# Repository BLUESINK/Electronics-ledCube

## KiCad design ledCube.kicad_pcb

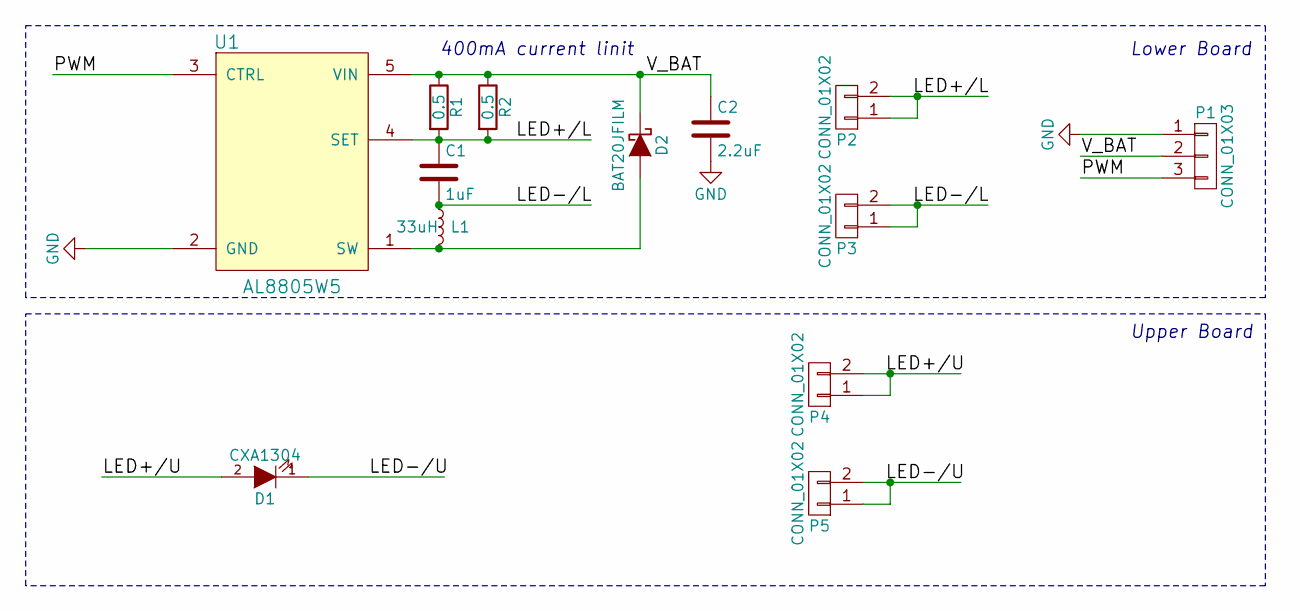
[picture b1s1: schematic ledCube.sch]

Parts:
C1: 1uF; C_0805
C2: 2.2uF; C_0805
D1: CXA1304; Part # CXA1304-0000-000N00B440F-ND
D2: BAT20JFILM; SOD-323_HandSoldering; Part # 497-3381-1-ND
L1: 33uH; inductor_33uH; Part # SRN6045-330MCT-ND
P1: CONN_01X03; Socket_Strip_Straight_1x03
P2, P3, P4, P5: CONN_01X02; Socket_Strip_Straight_1x02
R1, R2: 0.5; R_1206; Part # 311-0.5LWCT-ND
U1: AL8805W5; SOT-23-5; Part # AL8805W5-7DICT-ND

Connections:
/LED+/L: C1.1, P2.1, P2.2, R1.2, R2.2, U1.4 (SET)
/LED+/U: D1.2 (A), P4.1, P4.2
/LED-/L: C1.2, L1.1, P3.1, P3.2
/LED-/U: D1.1 (K), P5.1, P5.2
/PWM: P1.3, U1.3 (CTRL)
/V_BAT: C2.1, D2.1 (K), P1.2, R1.1, R2.1, U1.5 (VIN)
GND: C2.2, P1.1, U1.2 (GND)
unnamed: D2.2 (A), L1.2, U1.1 (SW)

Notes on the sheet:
400mA current linit
Lower Board
Upper Board

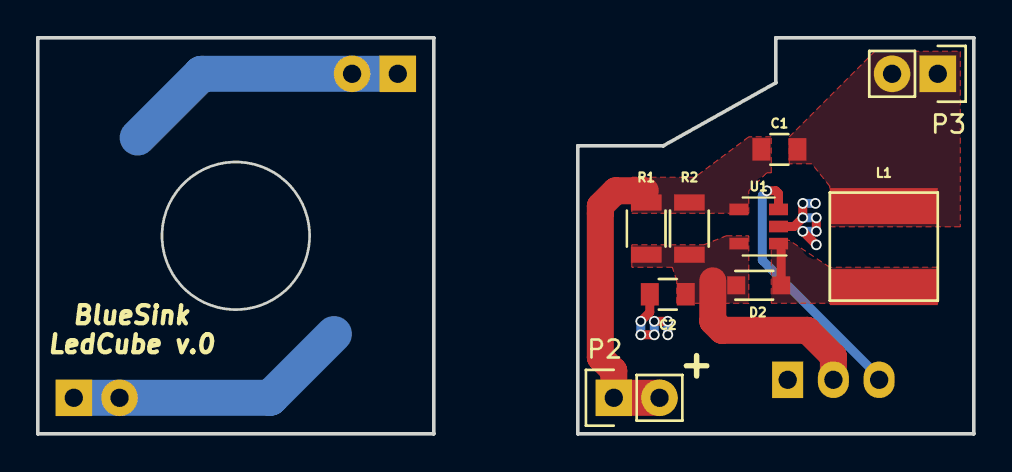
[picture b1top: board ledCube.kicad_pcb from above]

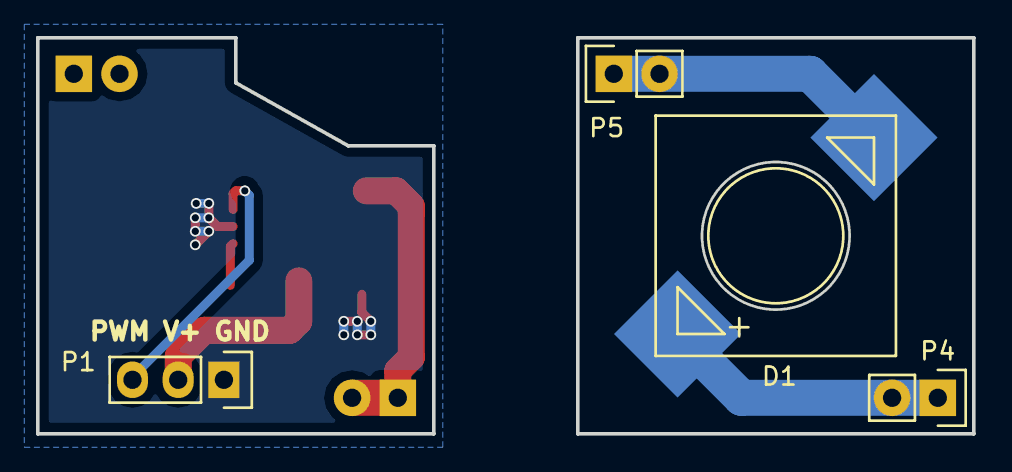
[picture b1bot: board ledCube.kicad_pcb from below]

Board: 2 copper layers, 52.0 x 22.0 mm, 13 parts (4 on the bottom side), 8 nets.

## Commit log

2016-12-28 Generate BOM & Gerber
2016-12-28 schematic upload
2017-01-02 pull down PWM line
